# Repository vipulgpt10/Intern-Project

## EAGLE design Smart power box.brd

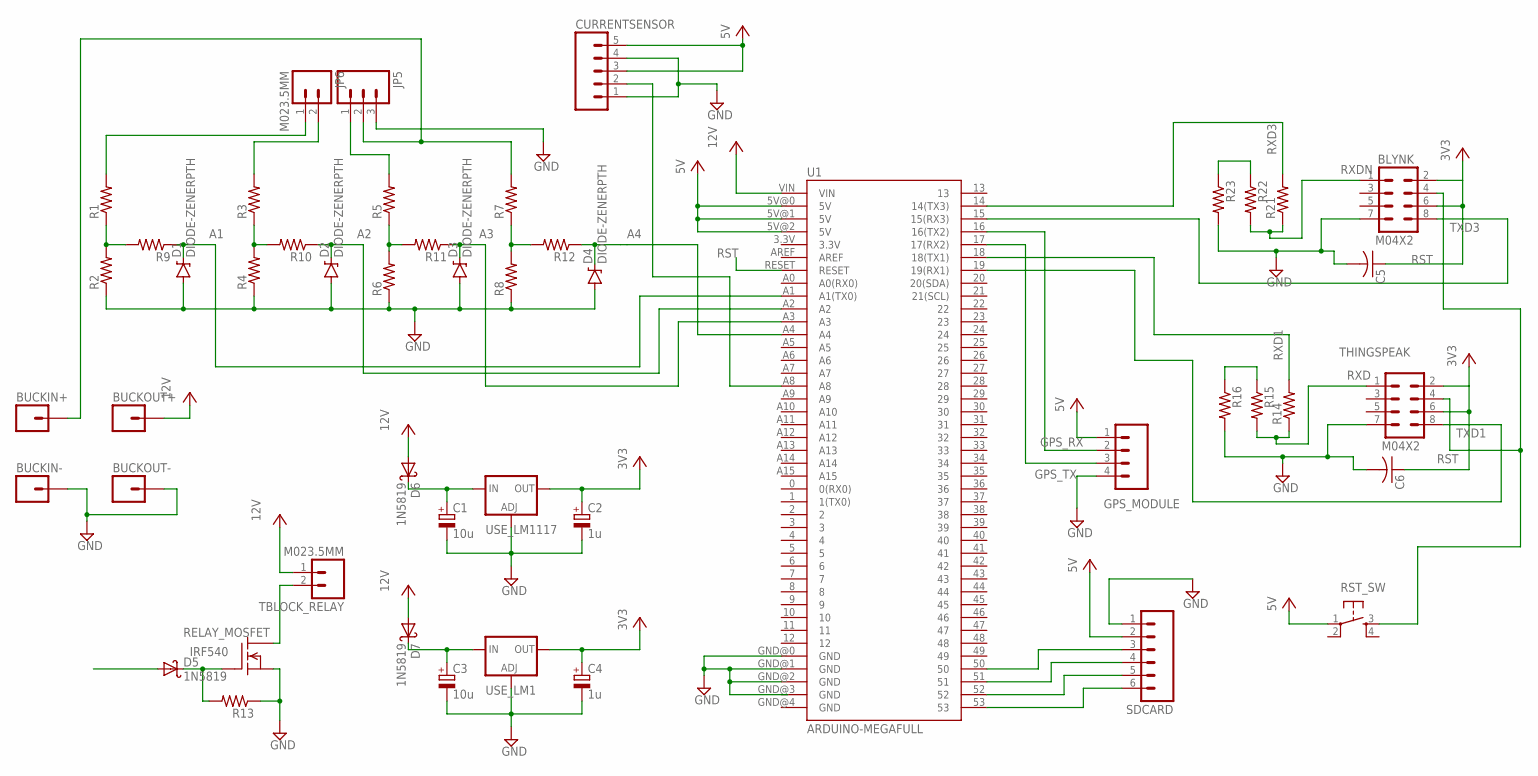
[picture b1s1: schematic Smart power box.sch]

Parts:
BLYNK: M04X2; 2X4
BUCKIN+: M01NOSILK-KIT; 1X01NS-KIT
BUCKIN-: M01NOSILK-KIT; 1X01NS-KIT
BUCKOUT+: M01NOSILK-KIT; 1X01NS-KIT
BUCKOUT-: M01NOSILK-KIT; 1X01NS-KIT
C1, C3: 10u; E2,5-6
C2, C4: 1u; E2,5-6
C5, C6: C-US025-024X044; C025-024X044
CURRENTSENSOR: M05JST-VERT; JST-5-PTH-VERT
D1, D2, D3, D4: DIODE-ZENERPTH; DIODE-ZENER
D5, D6, D7: 1N5819; DO41-10
GPS_MODULE: M04PTH; 1X04
JP5: M03SCREW; SCREWTERMINAL-3.5MM-3
JP6: M023.5MM; SCREWTERMINAL-3.5MM-2
R1, R2, R3, R4, R5, R6, R7, R8, R9, R10, R11, R12: R-US_0207/15; 0207/15
R13, R14, R15, R16, R21, R22, R23: R-US_0207/7; 0207/7
RELAY_MOSFET: IRF540; TO220
RST_SW: OMRON_SWITCH_40-XX; B3F-40XX
SDCARD: M06SILK_FEMALE_PTH; 1X06
TBLOCK_RELAY: M023.5MM; SCREWTERMINAL-3.5MM-2
THINGSPEAK: M04X2; 2X4
U1: ARDUINO-MEGAFULL; ARDUINO_MEGA
USE_LM1, USE_LM1117: V_REG_317SINK; TO220-ADJ

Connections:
A1: D1.P$1 (C), R9.1, U1.A1 (A1(TX0))
A2: D2.P$1 (C), R10.1, U1.A2
A3: D3.P$1 (C), R11.1, U1.A3
A4: D4.P$1 (C), R12.1, U1.A4
GND: BLYNK.7, BUCKIN-.1, BUCKOUT-.1, C1.-, C2.-, C3.-, C4.-, C5.2, C6.2, CURRENTSENSOR.1, CURRENTSENSOR.4, D1.P$2 (A), D2.P$2 (A), D3.P$2 (A), D4.P$2 (A), GPS_MODULE.4, JP5.3, R2.1, R4.1, R6.1, R8.1, R13.1, R16.2, R23.2, RELAY_MOSFET.3 (S), SDCARD.1, THINGSPEAK.7, U1.GND@0 (GND), U1.GND@1 (GND), U1.GND@2 (GND), USE_LM1.ADJ, USE_LM1117.ADJ
GPS_RX: GPS_MODULE.2, U1.16 (16(TX2))
GPS_TX: GPS_MODULE.3, U1.17 (17(RX2))
unnamed: R1.1, R2.2, R9.2
unnamed: R3.1, R4.2, R10.2
unnamed: R5.1, R6.2, R11.2
unnamed: R7.1, R8.2, R12.2
unnamed: C1.+, D6.C, USE_LM1117.IN
unnamed: CURRENTSENSOR.2, U1.A8
unnamed: SDCARD.3, U1.50
unnamed: SDCARD.4, U1.51
unnamed: JP6.1, R1.2
unnamed: JP6.2, R3.2
unnamed: JP5.1, R5.2
unnamed: BUCKIN+.1, JP5.2, R7.2
unnamed: RELAY_MOSFET.2 (D), TBLOCK_RELAY.2
unnamed: D5.C, R13.2, RELAY_MOSFET.1 (G)
unnamed: R15.1, R16.1
unnamed: SDCARD.5, U1.52
unnamed: SDCARD.6, U1.53
unnamed: C3.+, D7.C, USE_LM1.IN
unnamed: R22.1, R23.1
RST: BLYNK.4, RST_SW.3 (S), THINGSPEAK.4, U1.RESET
RXD: R14.1, R15.2, THINGSPEAK.1
RXD1: R14.2, U1.18 (18(TX1))
RXD3: R21.2, U1.14 (14(TX3))
RXDN: BLYNK.1, R21.1, R22.2
TXD1: THINGSPEAK.8, U1.19 (19(RX1))
TXD3: BLYNK.8, U1.15 (15(RX3))
VCC: BLYNK.2, BLYNK.6, BUCKOUT+.1, C2.+, C4.+, C5.1, C6.1, CURRENTSENSOR.3, CURRENTSENSOR.5, D6.A, D7.A, GPS_MODULE.1, RST_SW.1, SDCARD.2, TBLOCK_RELAY.1, THINGSPEAK.2, THINGSPEAK.6, U1.5V@0 (5V), U1.5V@1 (5V), U1.5V@2 (5V), U1.VIN, USE_LM1.OUT, USE_LM1117.OUT

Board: 2 copper layers, 49 parts (0 on the bottom side), 34 nets, no tracks yet.

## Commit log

2016-05-28 :octocat: Added .gitattributes & .gitignore files
2016-06-01 Create Eagle_SPB

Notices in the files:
parts and their libraries:
SparkFun-Boards: Licensing: Creative Commons ShareAlike 4.0 International - https://creativecommons.org/licenses/by-sa/4.0
